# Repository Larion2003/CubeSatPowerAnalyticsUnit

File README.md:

# TiSAT CubeSat - Power Analytics Unit 
 
This repository contains the design and development files for the Power Analytics Unit of the **TiSAT CubeSat** project. The primary objective is to monitor and analyze the power consumption of various sensors integrated into the satellite. 
 
## Project Overview 
The core of this project is a custom-designed power measurement circuit. It utilizes a **shunt resistor** to measure minute currents and voltage levels across specific circuit branches, enabling precise power calculation.  
 
Since the satellite is equipped with **solar panels** for battery charging, the power management logic accounts for both energy harvesting and consumption cycles to ensure balanced power distribution. 
 
## Current Progress
- [x] **Circuit Design:** Completed the schematic and PCB layout using **KiCad**.
- [x] **Component Selection:** Selected specialized ICs for precision current sensing (INA199A1) and the STM32L431KC microcontroller.
- [x] **Manufacturing & Assembly:** The custom PCB has been fully manufactured, and all SMD and through-hole components (including critical high-precision IC packages) have been successfully soldered and assembled.
- [x] **Firmware Communication Loop:** Established a low-level hardware communication interface between the STM32 MCU and a Raspberry Pi Pico W using single-wire, half-duplex UART with inverted polarity (open-drain transmitter, 9600 baud). The firmware is bare-metal and uses blocking (polling) USART access.
- [x] **Ping-Pong Verification:** As the first step, confirmed working end-to-end UART communication on the shared single-wire bus — the STM32 replied `pong\n` to every `ping\n` sent by the Raspberry Pi Pico W, verifying the physical link between the two microcontrollers.
- [x] **Shunt Resistor Calibration:** Performed a 4-point (Kelvin) measurement to precisely determine the shunt resistor's true value (52.2865 mΩ, not the nominal 50 mΩ).
- [x] **TiSAT Protocol Implementation:** Replaced the raw ping-pong test with the full, checksum-validated TiSAT frame protocol (`$`/`#` direction, 3-character module ID, payload, checksum, terminator), matching the shared master-side specification used across the TiSAT project's other modules.
- [x] **ADC-Based Power Measurement:** Implemented calibrated ADC sampling of the shunt voltage — using the internal VREFINT reference to compensate for real VDDA deviation and 64x oversampling to suppress noise — converting the INA199 current-sense amplifier output into live current, voltage and power readings, delivered over the `GETDATA` command.
- [x] **Current Calibration & Verification:** Calibrated the current measurement against known reference currents with a straight-line (linear regression) correction, and added a no-load threshold so an unloaded module reports exactly `0`. Verified on 38 reference points between 1 mA and 200 mA: the worst absolute error is 0.194 mA (about 0.1 % of the 200 mA range), the relative error is below 0.3 % from 50 mA up and reaches 8.7 % only at 1 mA, where one ADC step (about 0.31 mA) limits the resolution.

## Software Architecture & Development 
The software side consists of the low-level firmware of the onboard microcontroller and a test master for the receiving subsystem: 
1. **Custom HAL (Hardware Abstraction Layer):** Bare-metal foundational drivers written from scratch in **C++** to manage the MCU peripherals (RCC, GPIO, ADC, USART), without any vendor HAL or RTOS. 
2. **Request-Response Communication:** The STM32 acts as a Slave: it waits for a command frame from the Master (`ping`, `GETDATA`) and answers it over the shared open-drain bus. Reception and transmission use polling in the main loop, which keeps the firmware simple and its timing predictable. 
3. **Calibrated Measurement Pipeline:** Every `GETDATA` request is answered with fresh, calibrated current, voltage and power values, based on the VREFINT-compensated, 64x oversampled ADC readings and the linear-regression current calibration. 
4. **Subsystem Master (Test):** A CircuitPython-based test master on the Raspberry Pi Pico W periodically sends `ping` and `GETDATA` frames, prints the replies, and toggles a diagnostic heartbeat LED. 
 
## About the Author 
This project is being developed as part of my **undergraduate thesis** at the **University of Szeged (SZTE)**, under the guidance of my supervisor.  
 
It serves as a practical application of my ongoing studies in **C, C++, and Assembly**. This mission allows me to bridge the gap between hardware design and low-level software engineering while contributing to the **TiSAT satellite mission**. 
 
--- 
*Thank you for visiting this repository!*

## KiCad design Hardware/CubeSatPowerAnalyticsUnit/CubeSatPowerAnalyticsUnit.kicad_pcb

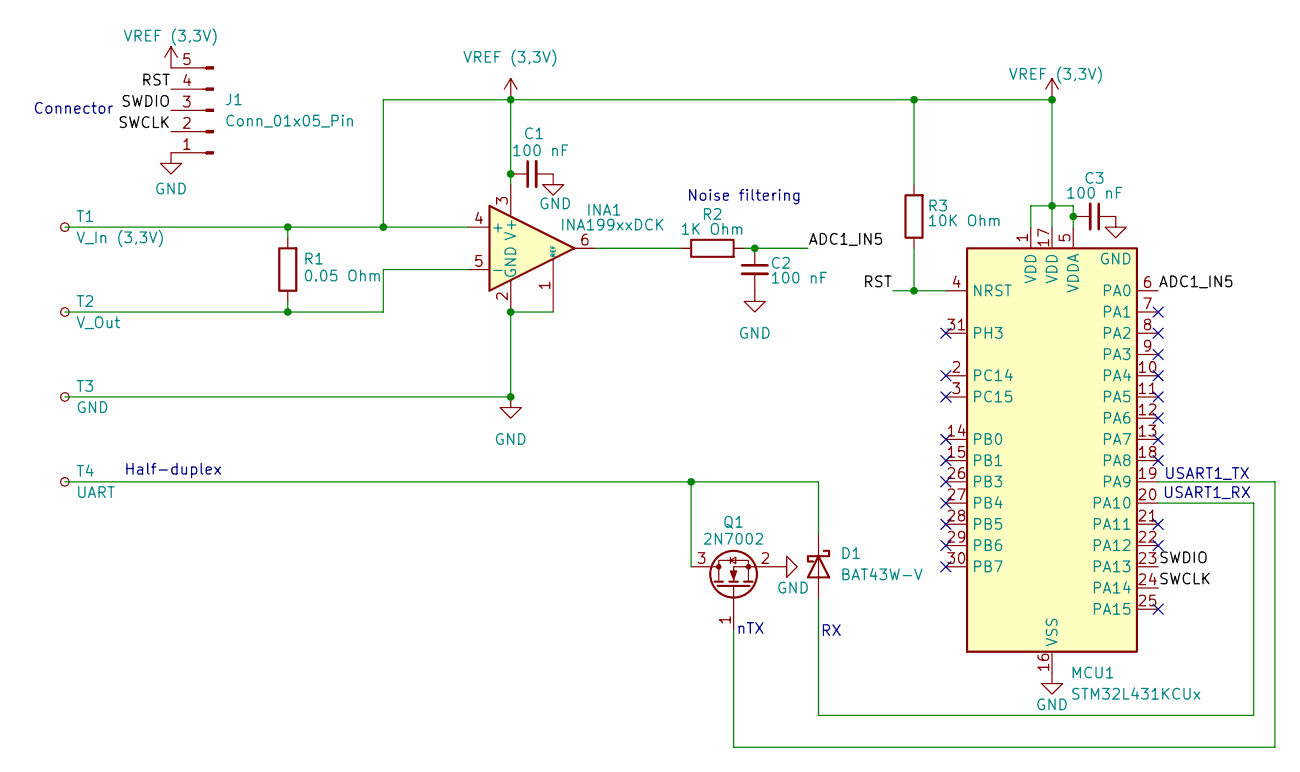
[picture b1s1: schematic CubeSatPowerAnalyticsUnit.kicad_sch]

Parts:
C1, C2, C3: 100 nF; C_0805_2012Metric_Pad1.18x1.45mm_HandSolder; LCSC C49678
D1: BAT43W-V; D_SOD-323_HandSoldering; LCSC C188548
INA1: INA199xxDCK; SOT-363_SC-70-6; LCSC C59135
J1: Conn_01x05_Pin; PinHeader_1x05_P2.54mm_Horizontal; LCSC C2883689
MCU1: STM32L431KCUx; QFN-32-1EP_5x5mm_P0.5mm_EP3.45x3.45mm; LCSC C1341298
Q1: 2N7002; SOT-23; LCSC C332103
R1: 0.05 Ohm; R_0805_2012Metric_Pad1.20x1.40mm_HandSolder; LCSC C49164908
R2: 1K Ohm; R_0805_2012Metric_Pad1.20x1.40mm_HandSolder; LCSC C2889523
R3: 10K Ohm; R_0805_2012Metric_Pad1.20x1.40mm_HandSolder; LCSC C17414
T1: V_In (3,3V); TestPoint_Pad_3.0x3.0mm
T2: V_Out; TestPoint_Pad_3.0x3.0mm
T3: GND; TestPoint_Pad_3.0x3.0mm
T4: UART; TestPoint_Pad_3.0x3.0mm

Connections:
/ADC1_IN5: C2.1, MCU1.6 (PA0), R2.2
/RST: J1.4, MCU1.4 (NRST), R3.1
/SWCLK: J1.2, MCU1.24 (PA14)
/SWDIO: J1.3, MCU1.23 (PA13)
GND: C1.2, C2.2, C3.1, INA1.1 (REF), INA1.2 (GND), J1.1, MCU1.16 (VSS), MCU1.32 (VSS), MCU1.33 (VSS), Q1.2 (S), T3.1
unnamed: D1.2 (A), MCU1.20 (PA10)
unnamed: D1.1 (K), Q1.3 (D), T4.1
unnamed: INA1.5 (-), R1.1, T2.1
unnamed: INA1.6, R2.1
unnamed: MCU1.19 (PA9), Q1.1 (G)
VREF (3,3V): C1.1, C3.2, INA1.3 (V+), INA1.4 (+), J1.5, MCU1.1 (VDD), MCU1.5 (VDDA), MCU1.17 (VDD), R1.2, R3.2, T1.1

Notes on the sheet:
Noise filtering
Half-duplex
USART1_RX
nTX
USART1_TX
Connector

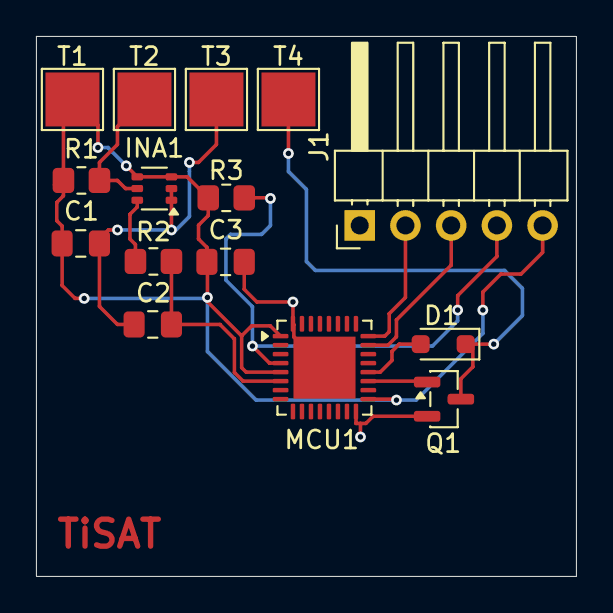
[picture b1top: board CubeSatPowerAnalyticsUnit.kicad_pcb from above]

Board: 2 copper layers, 30.0 x 30.0 mm, 15 parts (0 on the bottom side), 11 nets.

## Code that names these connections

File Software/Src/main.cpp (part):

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namespace {

    // -------------------------------- MEASUREMENT CHAIN --------------------------------
    // Load current -> shunt resistor -> INA199 (x50) -> ADC1 channel 5 (PA0).
    // The supply voltage (VDDA) is measured separately through the ADC's internal VREFINT channel.

    constexpr uint32_t ADC1_CHANNEL     = 5;          // PA0: INA199 output (amplified shunt voltage)
    constexpr uint32_t ADC_CH0_VREFINT  = 0;          // ADC channel 0: internal reference voltage (VREFINT)
    constexpr float    SHUNT_RESISTOR   = 0.0522865f; // Ohm: 52.2865 mOhm, measured with a 4-point method
    constexpr float    INA199_GAIN      = 50.0f;      // V/V: gain of the INA199A1 current-sense amplifier
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    // internal voltage regulator, calibrates the ADC and switches it on (power-up sequence from
    // the reference manual's ADC chapter).
    //
    // PA0 needs no GPIO setup: pins reset into analog mode, which is what the ADC input needs.
    void adc_init() {
        ADC1->CR &= ~ADC_CR_DEEPPWD;     // Wake up from deep-power-down (the reset state)
        ADC1->CR |= ADC_CR_ADVREGEN;     // Enable the ADC's internal voltage regulator
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
    // ==========================================================================
    // USART1 — 9600 baud on one shared bus wire
    // PA9 = USART1_TX, PA10 = USART1_RX. The USART runs in normal full-duplex mode, but both pins
    // are connected to the same bus wire, so every transmitted byte is also received (see send_frame).
    // ==========================================================================

    // Set PA9 and PA10 to alternate-function mode. PA13/PA14 (SWDIO/SWCLK) are left untouched:
    // they are already in alternate-function mode after reset, which keeps the debugger connected.
    GPIOA->MODER &= ~(GPIO_MODER_MODE9  | GPIO_MODER_MODE10);
    GPIOA->MODER |=  (GPIO_MODER_MODE9_1 | GPIO_MODER_MODE10_1);

    // Select AF7 (USART1) as the alternate function of PA9 and PA10.
    GPIOA->AFR[1] &= ~(GPIO_AFRH_AFSEL9 | GPIO_AFRH_AFSEL10);
    GPIOA->AFR[1] |=  (7u << GPIO_AFRH_AFSEL9_Pos) |
                      (7u << GPIO_AFRH_AFSEL10_Pos);
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    // Baud rate register: system clock / baud rate (4 MHz / 9600 = 416).
    USART1->BRR = USART1_BRR;

    // Invert the TX line. The board routes PA9 through an external hardware inverter; this
    // compensates for it and restores a non-inverted signal on the bus.
    USART1->CR2 |= USART_CR2_TXINV;

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
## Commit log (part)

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2026-02-23 Initial commit - KiCad project start
2026-02-25 Start PCB layout and initial routing.
2026-02-26 Initial commit - KiCad project v1.0
2026-02-26 Initial commit - KiCad project v1.1
2026-03-02 Initial commit - KiCad project v1.2
2026-03-22 Generate fabrication files - KiCad project v1.4
2026-03-22 Modify various footprints - KiCad project v1.5
2026-03-23 Fixing some issues - KiCad project v1.6
2026-04-07 Add project description - README.md v1.0
2026-04-16 Refactor project structure: separated hardware and software (History restored)
2026-04-22 Initialize USART1 and ADC1.
2026-04-28 Remove build artifacts (.o and .su files) from tracking
2026-04-28 Add local gitignore to Src folder
2026-04-28 Hardware Abstraction Layer: v1.0
2026-05-09 Hardware Abstraction Layer: v1.1
2026-05-28 Hardware Abstraction Layer: v1.2 - add syscalls.cpp file.
